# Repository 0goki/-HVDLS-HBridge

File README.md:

# -HVDLS-HBridge

H-Bridge breakout board for use with [High Voltage Digital Level Shifter project](https://github.com/0goki/HighVoltageDigitalLevelShifter/) to drive electromagnets with forward and reverse current.

## Revisions

| H-Bridge | Notes |
| ------------- | ------------- |
| HB01172026 | First physical production run with JLCPCB. KICAD Nightly 9.99 |

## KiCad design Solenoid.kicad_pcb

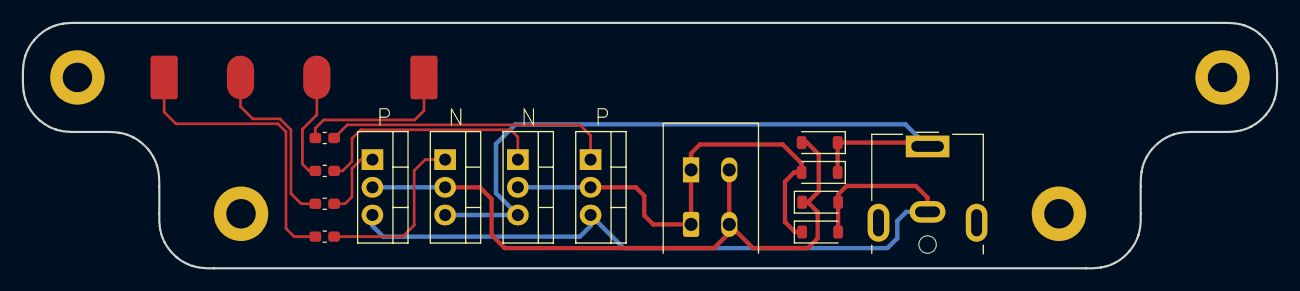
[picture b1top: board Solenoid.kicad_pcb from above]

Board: 2 copper layers, 115.0 x 22.5 mm, 20 parts (0 on the bottom side), 12 nets.

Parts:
D1, D2, D3, D4: 1N914; D_SOD-123
H1, H2, H3, H4: MountingHole_Pad; 6x2.7mm_MP
J1, J2: Conn_01x06_Pin; 01x06 POGO_1
J3: Conn_01x02_Socket; BarrelJack_CUI_PJ-063AH_Horizontal
J4: Conn_01x02_Socket; TerminalBlock_WAGO_2601-1106_1x02_P3.50mm_Horizontal
Q1, Q3: FQP27P06; TO-220-3_Vertical
Q2, Q4: IPP060N06N; TO-220-3_Vertical
R1, R2, R3, R4: 1K; C_0603_1608Metric_Pad1.08x0.95mm_HandSolder

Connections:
+DC: D1.1 (K), D3.1 (K), J3.1, Q1.3 (S), Q3.3 (S)
/OUT00: D1.2 (A), D2.1 (K), J4.2, Q1.2 (D), Q2.2 (D)
/OUT01: D3.2 (A), D4.1 (K), J4.1, Q3.2 (D), Q4.2 (D)
/PIN00: J1.1, R1.1
/PIN01: J1.3, R2.1
/PIN02: J1.5, R3.1
/PIN03: J2.1 (Pin_1_1), R4.1
GND: D2.2 (A), D4.2 (A), H1.1 (1_1), H2.1 (1_1), H3.1 (1_1), H4.1 (1_1), J3.2, Q2.3 (S), Q4.3 (S)
unnamed: Q1.1 (G), R1.2
unnamed: Q2.1 (G), R2.2
unnamed: Q3.1 (G), R3.2
unnamed: Q4.1 (G), R4.2

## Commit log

2026-01-21 Update README with project details and KICAD version
    Added project description and details for manufacturing.
2026-01-21 Update README with project image and description
    Added image and description for H-Bridge project.
2026-01-22 Revise README with project details and revisions
    Updated project description and added revisions section.
2026-01-22 Update README with detailed H-Bridge functionality
    Expanded description of the H-Bridge breakout board to include its functionality for driving electromagnets.
